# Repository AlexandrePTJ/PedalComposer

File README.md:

# PedalComposer
Pedal Fx Composer

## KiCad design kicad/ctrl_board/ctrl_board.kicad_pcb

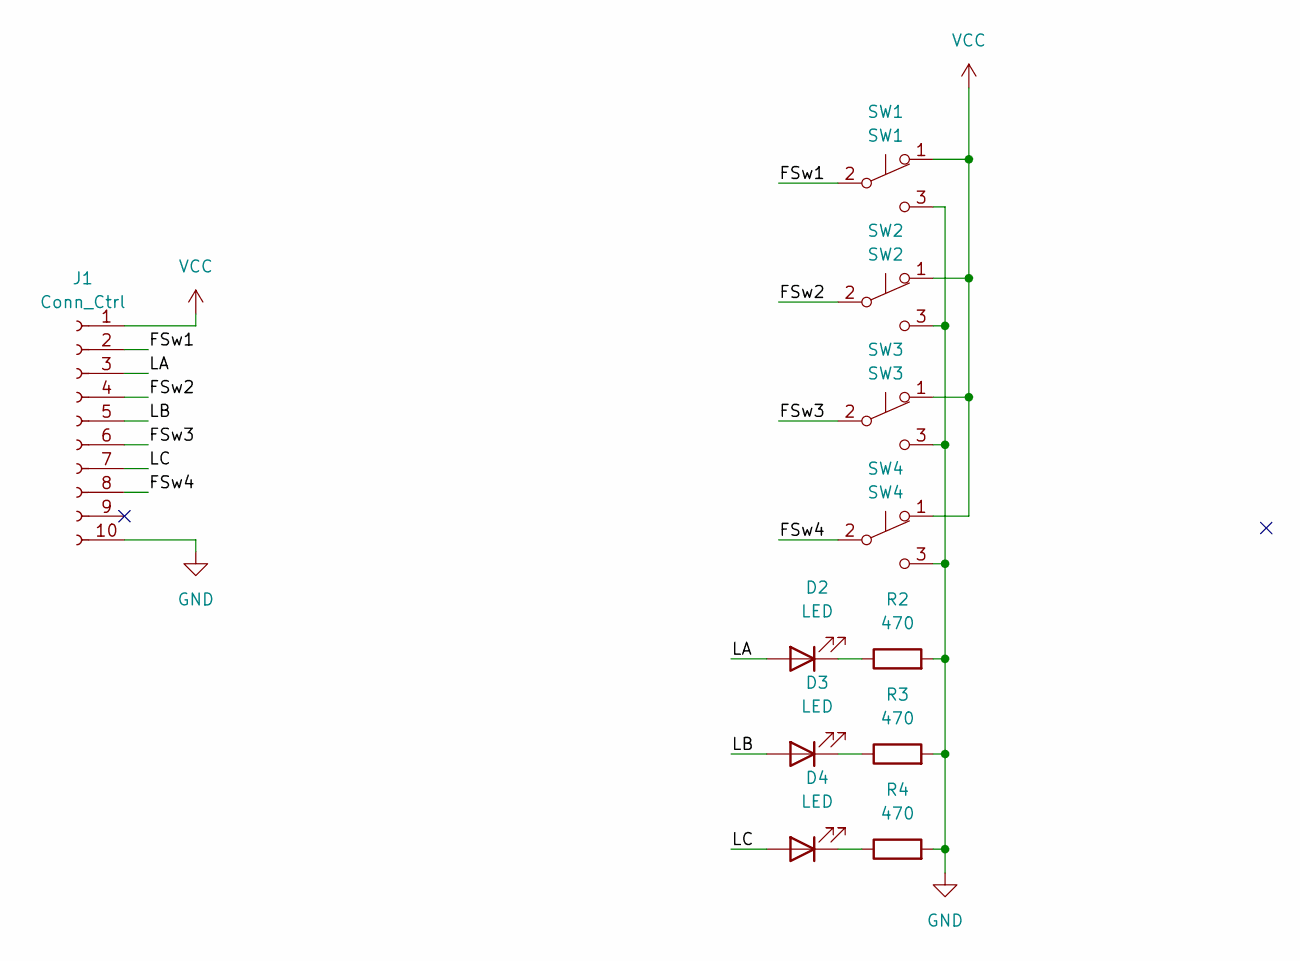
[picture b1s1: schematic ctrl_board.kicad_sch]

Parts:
D2, D3, D4: LED; LED_D3.0mm
J1: Conn_Ctrl; PinHeader_1x10_P2.54mm_Vertical
R2, R3, R4: 470; R_Axial_DIN0207_L6.3mm_D2.5mm_P7.62mm_Horizontal
SW1: SW1; SPDT Momentum
SW2: SW2; SPDT Momentum
SW3: SW3; SPDT Momentum
SW4: SW4; SPDT Momentum

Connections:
/FSw1: J1.2, SW1.2 (B)
/FSw2: J1.4, SW2.2 (B)
/FSw3: J1.6, SW3.2 (B)
/FSw4: J1.8, SW4.2 (B)
/LA: D2.2 (A), J1.3
/LB: D3.2 (A), J1.5
/LC: D4.2 (A), J1.7
GND: J1.10, R2.2, R3.2, R4.2, SW1.3 (C), SW2.3 (C), SW3.3 (C), SW4.3 (C)
unnamed: D2.1 (K), R2.1
unnamed: D3.1 (K), R3.1
unnamed: D4.1 (K), R4.1
VCC: J1.1, SW1.1 (A), SW2.1 (A), SW3.1 (A), SW4.1 (A)

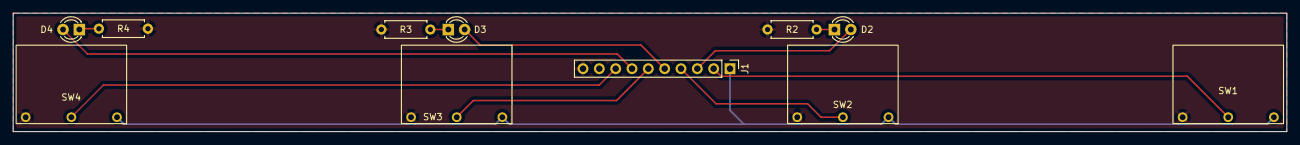
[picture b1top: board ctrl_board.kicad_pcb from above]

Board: 2 copper layers, 198.1 x 18.4 mm, 11 parts (0 on the bottom side), 12 nets.

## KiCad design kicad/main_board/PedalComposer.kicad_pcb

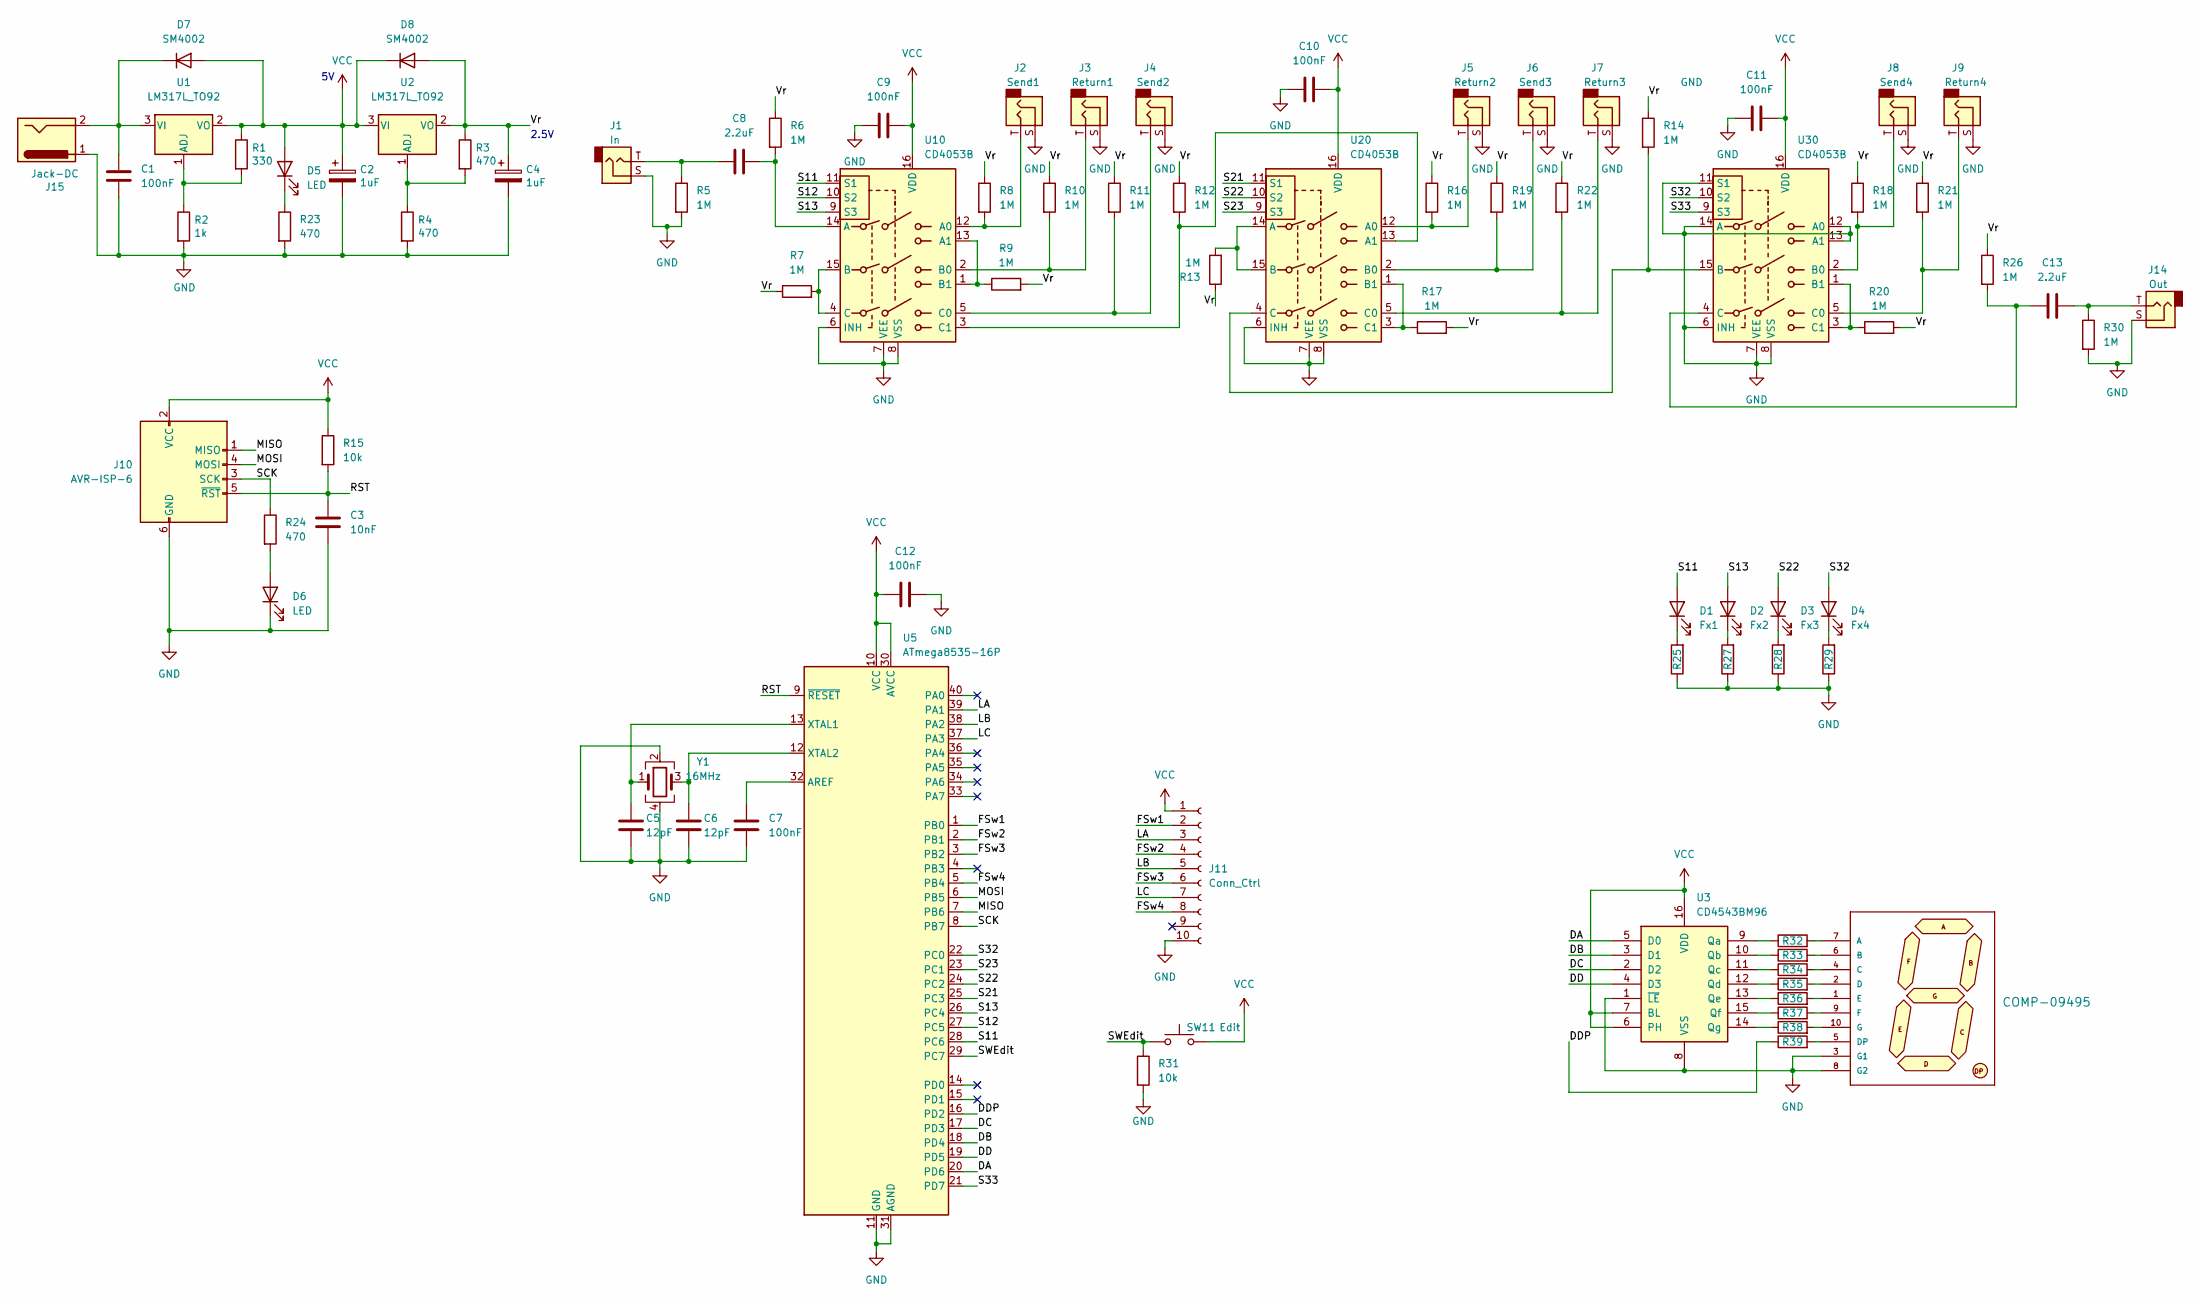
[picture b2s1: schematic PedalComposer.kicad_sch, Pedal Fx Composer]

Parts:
C1, C7, C9, C10, C11, C12: 100nF; C_0603_1608Metric; LCSC C14663
C2, C4: 1uF; CP_Elec_4x5.4; LCSC C72491
C3: 10nF; C_0603_1608Metric; LCSC C100042
C5, C6: 12pF; C_0603_1608Metric; LCSC C38523
C8, C13: 2.2uF; C_0805_2012Metric; LCSC C19110
D1: Fx1; LED_D3.0mm
D2: Fx2; LED_D3.0mm
D3: Fx3; LED_D3.0mm
D4: Fx4; LED_D3.0mm
D5, D6: LED; LED_0603_1608Metric; LCSC C2297
D7, D8: SM4002; D_SOD-123F; LCSC C151753
J1: In; Jack_6.35mm_Neutrik_NRJ4HF_Horizontal
J2: Send1; Jack_6.35mm_Neutrik_NRJ4HF_Horizontal
J3: Return1; Jack_6.35mm_Neutrik_NRJ4HF_Horizontal
J4: Send2; Jack_6.35mm_Neutrik_NRJ4HF_Horizontal
J5: Return2; Jack_6.35mm_Neutrik_NRJ4HF_Horizontal
J6: Send3; Jack_6.35mm_Neutrik_NRJ4HF_Horizontal
J7: Return3; Jack_6.35mm_Neutrik_NRJ4HF_Horizontal
J8: Send4; Jack_6.35mm_Neutrik_NRJ4HF_Horizontal
J9: Return4; Jack_6.35mm_Neutrik_NRJ4HF_Horizontal
J10: AVR-ISP-6; PinHeader_2x03_P2.54mm_Vertical; LCSC C65114
J11: Conn_Ctrl; PinHeader_1x10_P2.54mm_Vertical; LCSC C57369
J14: Out; Jack_6.35mm_Neutrik_NRJ4HF_Horizontal
J15: Jack-DC; BarrelJack_Horizontal
M1: 7-SEGMENT-1DIGIT-1INCH-BLUE; 7SegmentLED_LTS6760_LTS6780
R1: 330; R_0603_1608Metric; LCSC C23138
R2: 1k; R_0603_1608Metric; LCSC C21190
R3, R4, R23, R24, R25, R27, R28, R29, R32, R33, R34, R35, R36, R37, R38, R39: 470; R_0603_1608Metric; LCSC C23179
R5, R6, R7, R8, R9, R10, R11, R12, R13, R14, R16, R17, R18, R19, R20, R21, R22, R26, R30: 1M; R_0603_1608Metric; LCSC C22935
R15, R31: 10k; R_0603_1608Metric; LCSC C25804
SW11: Edit; SW_PUSH_6mm; LCSC C13828
U1, U2: LM317L_TO92; TO-92_Inline
U3: CD4543BM96; SOIC-16_3.9x9.9mm_P1.27mm; LCSC C28326
U5: ATmega8535-16P; DIP-40_W15.24mm_Socket; LCSC C2332
U10, U20, U30: CD4053B; DIP-16_W7.62mm_Socket; LCSC C2326
Y1: 16MHz; Crystal_SMD_3225-4Pin_3.2x2.5mm; LCSC C13738

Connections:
/DA: U3.5 (D0), U5.20 (PD6)
/DB: U3.3 (D1), U5.18 (PD4)
/DC: U3.2 (D2), U5.17 (PD3)
/DD: U3.4 (D3), U5.19 (PD5)
/DDP: R39.1, U5.16 (PD2)
/FSw1: J11.2, U5.1 (PB0)
/FSw2: J11.4, U5.2 (PB1)
/FSw3: J11.6, U5.3 (PB2)
/FSw4: J11.8, U5.5 (PB4)
/LA: J11.3, U5.39 (PA1)
/LB: J11.5, U5.38 (PA2)
/LC: J11.7, U5.37 (PA3)
/MISO: J10.1 (MISO), U5.7 (PB6)
/MOSI: J10.4 (MOSI), U5.6 (PB5)
/RST: C3.2, J10.5 (~RST), R15.2, U5.9 (~RESET)
/S11: D1.2 (A), U5.28 (PC6), U10.11 (S1)
/S12: U5.27 (PC5), U10.10 (S2)
/S13: D2.2 (A), U5.26 (PC4), U10.9 (S3)
/S21: U5.25 (PC3), U20.11 (S1)
/S22: D3.2 (A), U5.24 (PC2), U20.10 (S2)
/S23: U5.23 (PC1), U20.9 (S3)
/S32: D4.2 (A), U5.22 (PC0), U30.10 (S2)
/S33: U5.21 (PD7), U30.9 (S3)
/SCK: J10.3 (SCK), R24.1, U5.8 (PB7)
/SWEdit: R31.1, SW11.1, U5.29 (PC7)
/Vr: C4.1, D8.2 (A), R3.1, R6.1, R7.1, R8.1, R9.2, R10.1, R11.1, R12.1, R13.1, R14.1, R16.1, R17.2, R18.1, R19.1, R20.2, R21.1, R22.1, R26.1, U2.2 (VO)
GND: C1.2, C2.2, C3.1, C4.2, C5.2, C6.2, C7.2, C9.1, C10.1, C11.1, C12.2, D6.1 (K), J1.S, J2.S, J3.S, J4.S, J5.S, J6.S, J7.S, J8.S, J9.S, J10.6 (GND), J11.10, J14.S, J15.1, M1.3 (G1), M1.8 (G2), R2.2, R4.2, R5.2, R23.2, R25.1, R27.1, R28.1, R29.1, R30.2, R31.2, U3.1 (~LE), U3.8 (VSS), U5.11 (GND), U5.31 (AGND), U10.6 (INH), U10.7 (VEE), U10.8 (VSS), U20.6 (INH), U20.7 (VEE), U20.8 (VSS), U30.6 (INH), U30.7 (VEE), U30.8 (VSS), U30.11 (S1), U30.12 (A0), U30.13 (A1), U30.14 (A), Y1.2, Y1.4
unnamed: C1.1, D7.1 (K), J15.2, U1.3 (VI)
unnamed: C5.1, U5.13 (XTAL1), Y1.1
unnamed: C6.1, U5.12 (XTAL2), Y1.3
unnamed: C7.1, U5.32 (AREF)
unnamed: C8.1, J1.T, R5.1
unnamed: C8.2, R6.2, U10.14 (A)
unnamed: C13.1, R26.2, U30.4 (C)
unnamed: C13.2, J14.T, R30.1
unnamed: D1.1 (K), R25.2
unnamed: D2.1 (K), R27.2
unnamed: D3.1 (K), R28.2
unnamed: D4.1 (K), R29.2
unnamed: D5.1 (K), R23.1
unnamed: D6.2 (A), R24.2
unnamed: J2.T, R8.2, U10.12 (A0)
unnamed: J3.T, R10.2, U10.2 (B0)
unnamed: J4.T, R11.2, U10.5 (C0)
unnamed: J5.T, R16.2, U20.12 (A0)
unnamed: J6.T, R19.2, U20.2 (B0)
unnamed: J7.T, R22.2, U20.5 (C0)
unnamed: J8.T, R18.2, U30.2 (B0)
unnamed: J9.T, R21.2, U30.5 (C0)
unnamed: M1.1 (E), R36.2
unnamed: M1.2 (D), R35.2
unnamed: M1.4 (C), R34.2
unnamed: M1.5 (DP), R39.2
unnamed: M1.6 (B), R33.2
unnamed: M1.7 (A), R32.2
unnamed: M1.9 (F), R37.2
unnamed: M1.10 (G), R38.2
unnamed: R1.2, R2.1, U1.1 (ADJ)
unnamed: R3.2, R4.1, U2.1 (ADJ)
unnamed: R7.2, U10.4 (C), U10.15 (B)
unnamed: R9.1, U10.1 (B1), U10.13 (A1)
unnamed: R12.2, U10.3 (C1), U20.13 (A1)
unnamed: R13.2, U20.14 (A), U20.15 (B)
unnamed: R14.2, U20.4 (C), U30.15 (B)
unnamed: R17.1, U20.1 (B1), U20.3 (C1)
unnamed: R20.1, U30.1 (B1), U30.3 (C1)
unnamed: R32.1, U3.9 (Qa)
unnamed: R33.1, U3.10 (Qb)
unnamed: R34.1, U3.11 (Qc)
unnamed: R35.1, U3.12 (Qd)
unnamed: R36.1, U3.13 (Qe)
unnamed: R37.1, U3.15 (Qf)
unnamed: R38.1, U3.14 (Qg)
VCC: C2.1, C9.2, C10.2, C11.2, C12.1, D5.2 (A), D7.2 (A), D8.1 (K), J10.2 (VCC), J11.1, R1.1, R15.1, SW11.2, U1.2 (VO), U2.3 (VI), U3.6 (PH), U3.7 (BL), U3.16 (VDD), U5.10 (VCC), U5.30 (AVCC), U10.16 (VDD), U20.16 (VDD), U30.16 (VDD)

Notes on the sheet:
2.5V

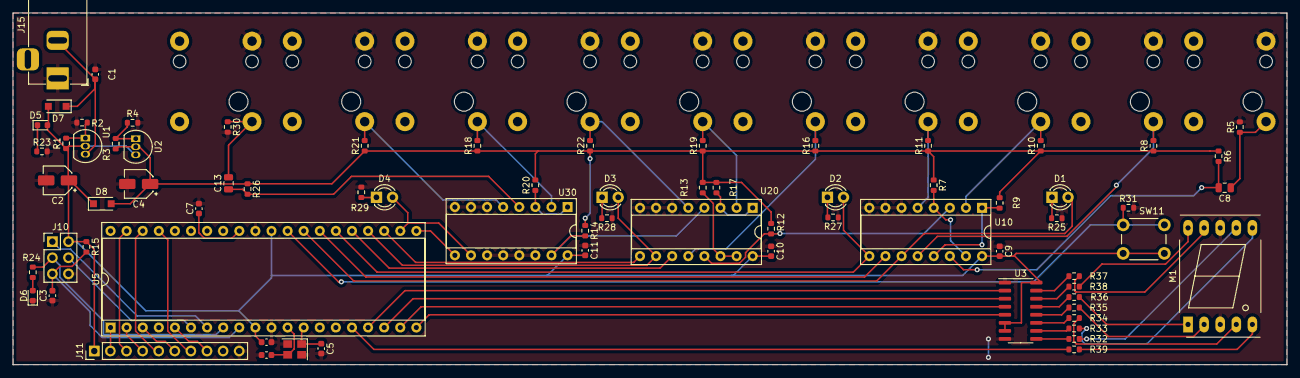
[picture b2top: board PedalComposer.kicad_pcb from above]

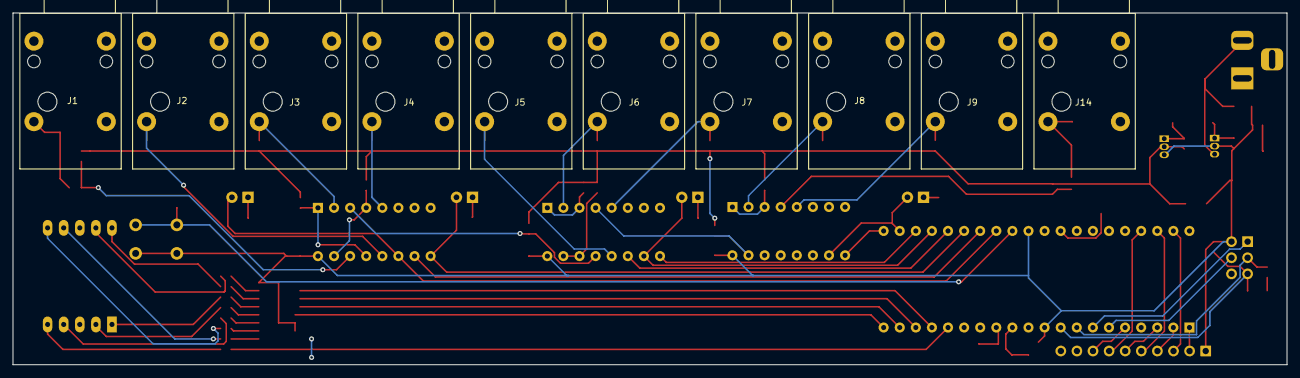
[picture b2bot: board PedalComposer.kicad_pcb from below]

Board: 2 copper layers, 201.0 x 55.5 mm, 83 parts (10 on the bottom side), 74 nets.

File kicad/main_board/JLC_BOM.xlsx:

| Comment | Designator | Footprint | Part
 | 10nF | C3 | Capacitor_SMD:C_0603_1608Metric | C100042
 | 1uF | C2, C4 | Capacitor_SMD:CP_Elec_4x5.4 | C72491
 | 12pF | C5, C6 | Capacitor_SMD:C_0603_1608Metric | C38523
 | 100nF | C1, C7, C9, C10, C11, C12 | Capacitor_SMD:C_0603_1608Metric | C14663
 | 2.2uF | C8, C13 | Capacitor_SMD:C_0805_2012Metric | C19110
 | LED | D5, D6 | LED_SMD:LED_0603_1608Metric | C2297
 | AVR-ISP-6 | J10 | Connector_PinHeader_2.54mm:PinHeader_2x03_P2.54mm_Vertical | C65114
 |  | J11 | Connector_PinHeader_2.54mm:PinHeader_1x10_P2.54mm_Vertical | C57369
 | 330 | R1 | Resistor_SMD:R_0603_1608Metric | C23138
 | 1k | R2 | Resistor_SMD:R_0603_1608Metric | C21190
 | 1M | R5, R6, R7, R8, R9, R10, R11, R12, R13, R14, R16, R17, R18, R19, R20, R21, R22,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 | Resistor_SMD:R_0603_1608Metric | C22935
 | 470 | R3, R4, R23, R24, R25, R27, R28, R29, R32, R33, R34, R35, R36, R37, R38, R39 | Resistor_SMD:R_0603_1608Metric | C23179
 | 10k | R15, R31 | Resistor_SMD:R_0603_1608Metric | C25804
 |  | SW11 | Button_Switch_THT:SW_PUSH_6mm | C13828
 |  | U3 | Package_SO:SOIC-16_3.9x9.9mm_P1.27mm | C28326
 |  | U5 | Package_DIP:DIP-40_W15.24mm_Socket | C2332
 |  | U10, U20, U30 | Package_DIP:DIP-16_W7.62mm_Socket | C2326
 | 16MHz | Y1 | Crystal:Crystal_SMD_3225-4Pin_3.2x2.5mm | C13738
 | SM4002 | D7, D8 | Diode_SMD:D_SOD-123F | C151753

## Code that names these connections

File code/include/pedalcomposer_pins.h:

#ifndef BDM_PEDAL_COMPOSER_PINS_H
#define BDM_PEDAL_COMPOSER_PINS_H

// Footswitchs LEDS
static const int PIN_LA = 39;
static const int PIN_LB = 38;
static const int PIN_LC = 37;

// Footswitchs
static const int PIN_FSW1 = 1;
static const int PIN_FSW2 = 2;
static const int PIN_FSW3 = 3;
static const int PIN_FSW4 = 5;

// Audio switches BCD
static const int PIN_S11 = 28;
static const int PIN_S12 = 27;
static const int PIN_S13 = 26;
static const int PIN_S21 = 25;
static const int PIN_S22 = 24;
static const int PIN_S23 = 23;
// static const int PIN_S31 = ; // NC
static const int PIN_S32 = 22;
static const int PIN_S33 = 21;

// 7-Segments drivers + dot
static const int PIN_DA = 20;
static const int PIN_DB = 18;
static const int PIN_DC = 17;
static const int PIN_DD = 19;
static const int PIN_DDP = 16;

#endif // BDM_PEDAL_COMPOSER_PINS_H

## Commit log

2022-11-01 Add schematics
2022-11-03 Add uC code
2022-11-04 Handle display
2022-11-15 Update sch, down to 4 Fx
2022-11-16 Update ignore
2022-11-16 WIP layout
2022-11-23 Update PCB
2022-12-11 Boards v1
2022-12-11 WIP code
